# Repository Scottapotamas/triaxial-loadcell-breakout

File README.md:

# Triaxial Load Cell Interface Breakout

Sourcing the NAU7802 seems easier than the HX711, and I2C suits my application nicely. The NAU7802 featured on [Sparkfun's Qwiic Scale breakout board](https://learn.sparkfun.com/tutorials/qwiic-scale-hookup-guide) has a hardcoded single I2C address, meaning only *one* loadcell can be put on a single I2C bus. 

I wanted to connect a triaxial load cell (3-dof, translational +- in xyz), so this breakout board puts 3x NAU7802 behind an I2C mux, a Texas Instruments TCA9548 8-channel mux (only channels 0, 1, 2 are used).

Access to the second analog channel of the NAU7802 is provided with the intent of connecting 10k NTC thermistors. This could be used for monitoring the load cell temperature (or multiple load cells if they aren't a single unit). For my application these monitor the temperatures of other elements undergoing temperature cycling.

## Hardware

A Qwiic header is included as a 'backwards compatibility layer' to the existing breakout design. If no software changes are made to Sparkfun's examples, the first channel of this board should behave identically to the single-channel Sparkfun breakout.

The 2.54mm header provides I2C, mux reset, and the ADC data-ready pins.

The solder jumpers labelled `0`, `1` and `2` change the I2C address of the I2C multiplexer. With the jumpers untouched, the address of the mux is `0x70`. These allow addresses between `0x70` to `0x77` to be used.

The general software flow is as follows:

- Telling the TCA9548 mux which output you want to use, (write `1 << channelNum` at `0x70`)
- Configure and read the NAU7802 at it's fixed base address of `0x2A`.
- Change the I2C mux to the next channel, configure and sample, repeat across channels.

Optionally, the data-ready pins of the 3 NAU7802 load cell amplifiers are exposed on the header, and these can indicate when a given load cell has completed aquisition and is ready for read-out.

### Multiple breakouts on one bus

If connecting multiple of these 3-axis boards to the same I2C bus, set the mux to a empty channel when accessing another board, as there can only be the *one* NAU7802 on the bus. By selecting an empty channel on the other breakouts, there won't be any conflicts.

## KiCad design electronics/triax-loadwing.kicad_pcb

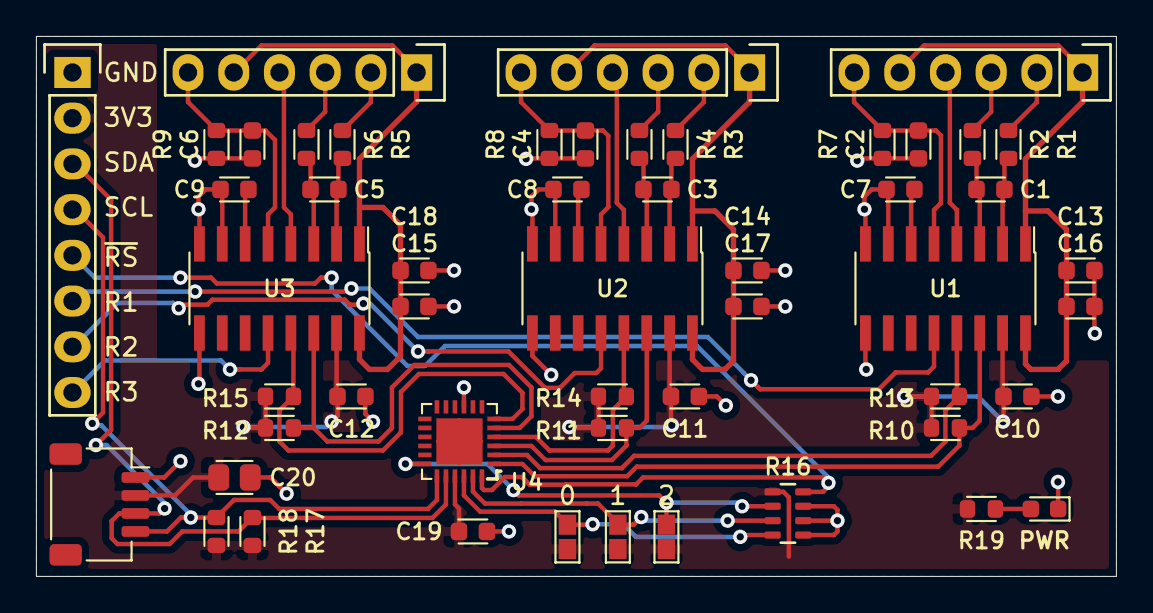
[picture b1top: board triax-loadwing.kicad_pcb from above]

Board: 2 copper layers, 60.0 x 30.0 mm, 52 parts (0 on the bottom side), 39 nets.

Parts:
C1, C3, C5, C7, C8, C9, C13, C14, C15: 100n_X7R_1608M; CAPC1608X90N
C2, C4, C6, C10, C11, C12: 100n_1608M; CAPC1608X90N
C16, C17, C18, C19: 1u_X7R_1608M; CAPC1608X90N
C20: 10u_X7R_2012M; CAPC2012X110N
D1: LED_RED_1608M; LEDC1608X80L40N
JP1, JP2, JP3: JUMPER-LINK-2; SJ1608-2N
P1, P2, P3: CONN_01X06; 61300611121
P4: CONN_01X08; 61300811121
P5: JST_SH_4_RA; SM04B-SRSS-TB
R1, R2, R3, R4, R5, R6: 47R_1608M; RESC1608X50N
R7, R8, R9, R10, R11, R12, R13, R14, R15, R17, R18: 4K7_1608M; RESC1608X50N
R16: 10K_QUAD_1608M; R_Array_Concave_4x1608M
R19: 1K00_1608M; RESC1608X50N
U1, U2, U3: NAU7802; SOIC16P127_990X600X175L83X41N
U4: TCA9548A; QFN25P50_400X400X100L40X24T270N

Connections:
+3.3V: C10.1, C11.1, C12.1, C19.1, C20.2, JP1.2, JP2.2, JP3.2, P4.2, P5.2, R10.2, R11.2, R12.2, R13.1, R14.1, R15.1, R16.1, R17.2, R18.1, R19.1, U1.15, U2.15, U3.15, U4.21
/ADC_PWR_1: C13.2, C16.1, P1.1, P1.5, U1.1, U1.16
/ADC_PWR_2: C14.2, C17.1, P2.1, P2.5, U2.1, U2.16
/ADC_PWR_3: C15.2, C18.1, P3.1, P3.5, U3.1, U3.16
GND: C2.2, C4.2, C6.2, C7.1, C8.1, C9.1, C10.2, C11.2, C12.2, C13.1, C14.1, C15.1, C16.2, C17.2, C18.2, C19.2, C20.1, D1.C, P1.4, P2.4, P3.4, P4.1, P5.1, R7.2, R8.2, R9.2, R16.5, R16.6, R16.7, U1.4, U1.7, U1.8, U1.9, U2.4, U2.7, U2.8, U2.9, U3.4, U3.7, U3.8, U3.9, U4.9
unnamed: C1.1, R1.1, U1.2
unnamed: C1.2, R2.1, U1.3
unnamed: C2.1, P1.6, R7.1, U1.5
unnamed: C3.1, R3.1, U2.2
unnamed: C3.2, R4.1, U2.3
unnamed: C4.1, P2.6, R8.1, U2.5
unnamed: C5.1, R5.1, U3.2
unnamed: C5.2, R6.1, U3.3
unnamed: C6.1, P3.6, R9.1, U3.5
unnamed: C7.2, U1.6
unnamed: C8.2, U2.6
unnamed: C9.2, U3.6
unnamed: D1.A, R19.2
unnamed: JP1.1, R16.4, U4.22
unnamed: JP2.1, R16.3, U4.23
unnamed: JP3.1, R16.2, U4.18
unnamed: P1.2, R1.2
unnamed: P1.3, R2.2
unnamed: P2.2, R3.2
unnamed: P2.3, R4.2
unnamed: P3.2, R5.2
unnamed: P3.3, R6.2
unnamed: R10.1, U1.14, U4.1
unnamed: R11.1, U2.14, U4.3
unnamed: R12.1, U3.14, U4.5
unnamed: R13.2, U1.13, U4.2
unnamed: R14.2, U2.13, U4.4
unnamed: R15.2, U3.13, U4.6
READY_1: P4.6, U1.12
READY_2: P4.7, U2.12
READY_3: P4.8, U3.12
SCL: P4.4, P5.4, R18.2, U4.19
SDA: P4.3, P5.3, R17.1, U4.20
~RESET: P4.5, R16.8, U4.24

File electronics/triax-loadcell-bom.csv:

Title:,Triaxial Loadcell Breakout,,,,,,
Rev:,V1.0,,,,,,
Source:,/Users/scott/projects/triaxial-loadcell-breakout/electronics/triax-loadwing.sch,,,,,,
Date:,"Tuesday, 28 May 2019 at 11:49:19 am",,,,,,
Component Count:,52,,,,,,
,,,,,,,
Ref,Qty,Value,Description,Manf,Manf#,Installed,Footprint
"C1, C3, C5, C7, C8, C9, C13, C14, C15",9,100n_X7R_1608M,"CAP, MLCC, X7R, 100NF, 50V, 0603",KEMET,C0603C104K5RACAUTO, ,CAPC1608X90N
"C16, C17, C18, C19",4,1u_X7R_1608M,"CAP, MLCC, X7R, 1UF, 50V, 0603",muRata,GRM188R61H105KAALD, ,CAPC1608X90N
"C2, C4, C6, C10, C11, C12",6,100n_1608M,"CAP, MLCC, X7R, 100NF, 50V, 0603",KEMET,C0603C104K5RACAUTO, ,CAPC1608X90N
C20,1,10u_X7R_2012M,"CAP, MLCC, X7R, 10UF, 6.3V, 0805, 2012M",MULTICOMP,MC0805B106K6R3CT, ,CAPC2012X110N
D1,1,LED_RED_1608M,"DIALIGHT ChipLED Red, 0603, 1608M",DIALIGHT,5988010107F, ,LEDC1608X80L40N
"JP1, JP2, JP3",3,JUMPER-LINK-2,,,,DNP,SJ1608-2N
"P1, P2, P3",3,CONN_01X06,"Pin Header, 2.54mm, Vertical, PTH, 6 Way, 1 Row, 01x06",WURTH,61300611121,DNP,61300611121
P4,1,CONN_01X08,"Pin Header, 2.54mm, Vertical, PTH, 8 Way, 1 Row, 01x08",WURTH,61300811121,DNP,61300811121
P5,1,JST_SH_4_RA,"JST SH/SR Series, 1.00mm Pitch, 4 Way, Shrouded Right Angle, PCB Header, Surface Mount",JST,SM04B-SRSS-TB(LF)(SN), ,SM04B-SRSS-TB
"R1, R2, R3, R4, R5, R6",6,47R_1608M,"RESISTOR, THICK FILM, 47R, 100mW, 0603, 1608M",PANASONIC,ERJ3GEYJ470V, ,RESC1608X50N
R16,1,10K_QUAD_ARRAY_1608M,"RESISTOR, THICK FILM, 10K, 5%, 0603, 1608M, QUAD ARRAY",BI TECHNOLOGIES,BCN164A103J7, ,R_Array_Concave_4x1608M
R19,1,1K00_1608M,"RESISTOR, THICK FILM, 1K, 125mW, 1%, 0603, 1608M",MULTICOMP,MCHP03W8F1001T5E, ,RESC1608X50N
"R7, R8, R9, R10, R11, R12, R13, R14, R15, R17, R18",11,4K7_1608M,"RESISTOR, THICK FILM, 100K, 125mW, 1%, 0603, 1608M",MULTICOMP,MC0063W060354K7, ,RESC1608X50N
"U1, U2, U3",3,NAU7802,"A/D Converter, 24-Bit, 2-input, Delta-Sigma, load/bridge whetstone sensors, I2C Interface, 2.7V-5.5V",Nuvoton, NAU7802SGI, ,SOIC16P127_990X600X175L83X41N
U4,1,TCA9548A,"I2C 8-channel multiplexer, 8:1 mux, 1.65-5.5V, 24QFN",TEXAS INSTRUMENTS,TCA9548ARGER , ,QFN25P50_400X400X100L40X24T270N
,,,,,,,
Tool:,Eeschema (5.1.0-0),,,,,,
Script:,/Users/scott/projects/ecad/scripts/BOM/bom/BOM-GroupedByValue.py,,,,,,

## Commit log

2019-05-14 Started schematic
2019-05-16 Fleshing out schematic
2019-05-16 Adds datasheets to /electronics/docs
2019-05-20 Fleshing out schematic - removed feather compatibility
2019-05-20 Readme updates
2019-05-21 PCB started
2019-05-21 Adds image to readme
2019-05-21 Adds board renders
2019-05-21 Routing complete
2019-05-21 Load cell datasheet
2019-05-28 Cosmetics final pass
2019-05-28 Titleblocks, pcb manf notes
2019-05-28 Added concept block diagram and pcb renders to README
    Also improves docs
2019-05-28 PDF exports
2019-05-28 Gerber export
2019-05-28 BOM for fab
    CSV and HTML with parts links
